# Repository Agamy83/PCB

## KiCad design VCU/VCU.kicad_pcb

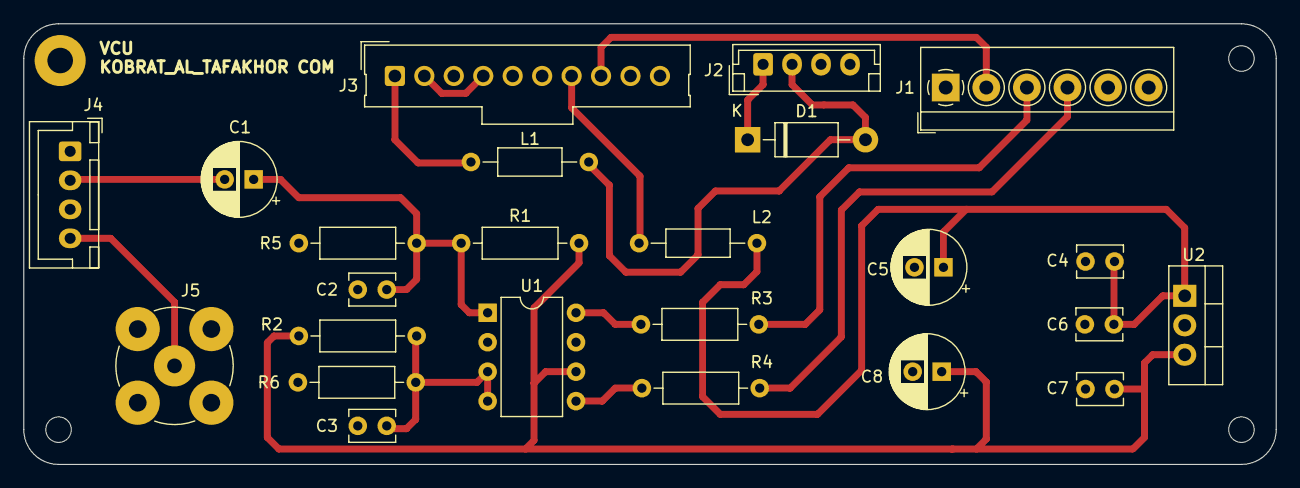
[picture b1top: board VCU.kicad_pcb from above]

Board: 2 copper layers, 108.0 x 38.0 mm, 28 parts (0 on the bottom side), 17 nets.

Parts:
C1: 220u; CP_Radial_D6.3mm_P2.50mm
C2: 680p; C_Disc_D3.8mm_W2.6mm_P2.50mm
C3, C4, C6, C7: 100n; C_Disc_D3.8mm_W2.6mm_P2.50mm
C5: 4u7; CP_Radial_D6.3mm_P2.50mm
C8: 100u; CP_Radial_D6.3mm_P2.50mm
D1: 1N4007; D_DO-41_SOD81_P10.16mm_Horizontal
H1: MountingHole_Pad; MountingHole_2.2mm_M2_Pad
H2, H3, H4: MountingHole; MountingHole_2.2mm_M2
J1: LEMO6; TerminalBlock_4Ucon_1x06_P3.50mm_Horizontal
J2: LEMO4; JST_EH_B4B-EH-A_1x04_P2.50mm_Vertical
J3: Conn_01x10_Male; Molex_SL_171971-0010_1x10_P2.54mm_Vertical
J4: Conn_01x04_Male; JST_XH_B4B-XH-A_1x04_P2.50mm_Vertical
J5: Conn_Coaxial; BNC_TEConnectivity_1478204_Vertical
L1, L2: 1uf; L_Axial_L5.3mm_D2.2mm_P10.16mm_Horizontal_Vishay_IM-1
R1, R2, R6: 10k; R_Axial_DIN0207_L6.3mm_D2.5mm_P10.16mm_Horizontal
R3, R4: 50R; R_Axial_DIN0207_L6.3mm_D2.5mm_P10.16mm_Horizontal
R5: 75R; R_Axial_DIN0207_L6.3mm_D2.5mm_P10.16mm_Horizontal
U1: EL2140; DIP-8_W7.62mm
U2: LM7808_TO220; TO-220-3_Vertical

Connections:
12V: C4.1, C5.1, C6.1, L2.1, U2.1 (VI)
+8V: C7.1, C8.1, R1.2, R2.1, U1.6 (Vcc), U2.3 (VO)
/J1_2_to_J3_8: J1.2, J3.8
/J3_1_to_L2: J3.1, L1.1
/TWISTED_PAIR_out_to_J2: J1.3, R3.2
/TWISTED_PAIR_outb_to_J2: J1.4, R4.2
/Video_1_to_C1: C1.2, J4.2
/Video_2_to_J5: J4.4, J5.1 (In)
GND: C2.2, C3.2, C4.2, C5.2, C6.2, C7.2, C8.2, H1.1, J1.6, J2.4, J3.9, J4.1, J4.3, J5.2 (Ext), R5.2, R6.2, U1.7 (Vee), U2.2 (GND)
unnamed: D1.2 (A), J2.2, L1.2
unnamed: D1.1 (K), J2.1
unnamed: J3.2, J3.4
unnamed: J3.7, L2.2
unnamed: C1.1, C2.1, R1.1, R5.1, U1.1 (Vin)
unnamed: C3.1, R2.2, R6.1, U1.3 (Vinb), U1.4 (Vref)
unnamed: R3.1, U1.8 (Vout)
unnamed: R4.1, U1.5 (Voutb)

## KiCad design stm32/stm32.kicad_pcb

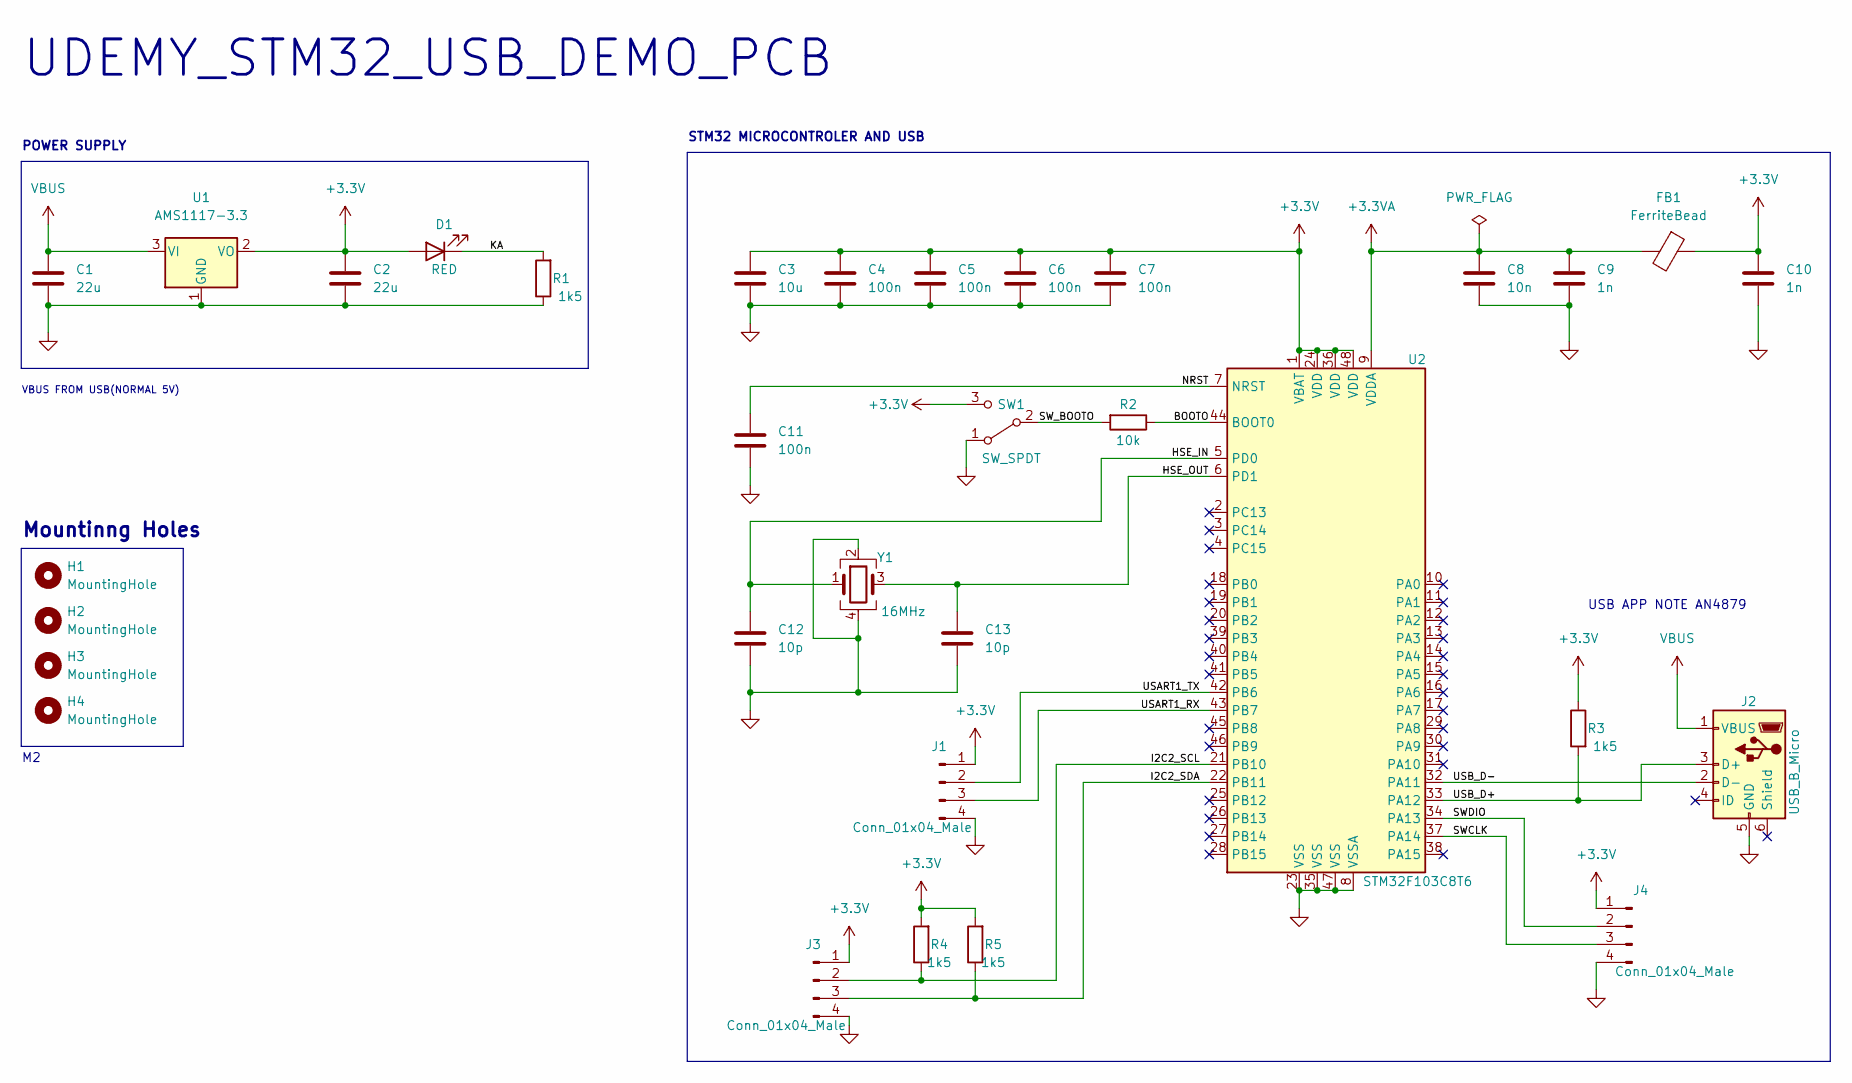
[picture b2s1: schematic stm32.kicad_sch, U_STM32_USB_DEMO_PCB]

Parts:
C1, C2: 22u; C_0805_2012Metric
C3: 10u; C_0603_1608Metric
C4, C5, C6, C7, C11: 100n; C_0402_1005Metric
C8: 10n; C_0402_1005Metric
C9, C10: 1n; C_0402_1005Metric
C12, C13: 10p; C_0402_1005Metric
D1: RED; LED_0603_1608Metric
FB1: FerriteBead; L_0603_1608Metric
H1, H2, H3, H4: MountingHole; MountingHole_2.2mm_M2
J1, J3, J4: Conn_01x04_Male; PinHeader_1x04_P2.54mm_Vertical
J2: USB_B_Micro; USB_Micro-B_Wuerth_629105150521
R1, R3, R4, R5: 1k5; R_0402_1005Metric
R2: 10k; R_0402_1005Metric
SW1: SW_SPDT; SW_SPDT_PCM12
U1: AMS1117-3.3; SOT-223-3_TabPin2
U2: STM32F103C8T6; LQFP-48_7x7mm_P0.5mm
Y1: 16MHz; Crystal_SMD_3225-4Pin_3.2x2.5mm

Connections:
+3.3V: C2.1, C3.1, C4.1, C5.1, C6.1, C7.1, C10.1, D1.2 (A), FB1.1, J1.1, J3.1, J4.1, R3.1, R4.2, R5.2, SW1.3 (C), U1.2 (VO), U2.1 (VBAT), U2.24 (VDD), U2.36 (VDD), U2.48 (VDD)
+3.3VA: C8.1, C9.1, FB1.2, U2.9 (VDDA)
/BOOTO: R2.1, U2.44 (BOOT0)
/HSE_IN: C12.1, U2.5 (PD0), Y1.1
/HSE_OUT: C13.1, U2.6 (PD1), Y1.3
/I2C2_SCL: J3.2, R4.1, U2.21 (PB10)
/I2C2_SDA: J3.3, R5.1, U2.22 (PB11)
/KA: D1.1 (K), R1.2
/NRST: C11.1, U2.7 (NRST)
/SWCLK: J4.3, U2.37 (PA14)
/SWDIO: J4.2, U2.34 (PA13)
/SW_BOOTO: R2.2, SW1.2 (B)
/USART1_RX: J1.3, U2.43 (PB7)
/USART1_TX: J1.2, U2.42 (PB6)
/USB_D+: J2.3 (D+), R3.2, U2.33 (PA12)
/USB_D-: J2.2 (D-), U2.32 (PA11)
GND: C1.2, C2.2, C3.2, C4.2, C5.2, C6.2, C7.2, C8.2, C9.2, C10.2, C11.2, C12.2, C13.2, J1.4, J2.5 (GND), J3.4, J4.4, R1.1, SW1.1 (A), U1.1 (GND), U2.8 (VSSA), U2.23 (VSS), U2.35 (VSS), U2.47 (VSS), Y1.2, Y1.4
VBUS: C1.1, J2.1 (VBUS), U1.3 (VI)

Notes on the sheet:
STM32 MICROCONTROLER AND USB
UDEMY_STM32_USB_DEMO_PCB
Mountinng Holes
USB APP NOTE AN4879
POWER SUPPLY
VBUS FROM USB(NORMAL 5V)

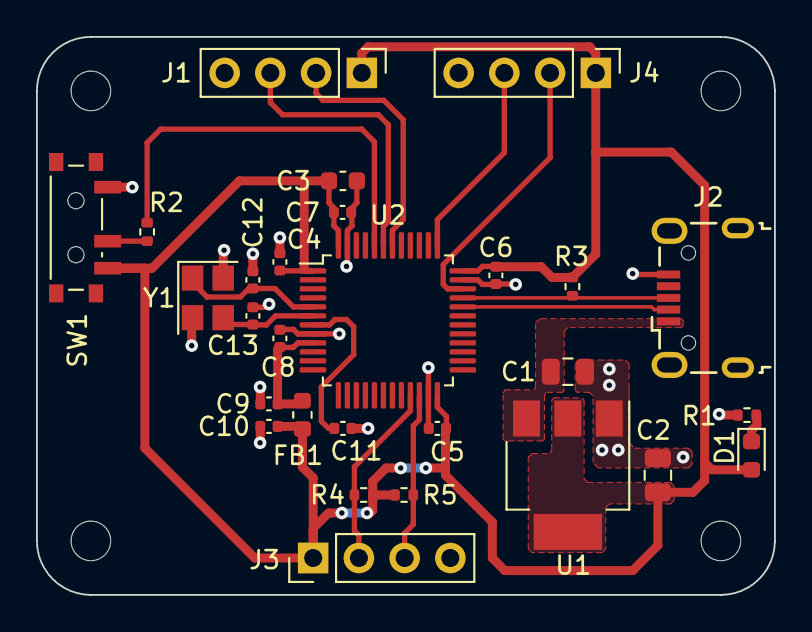
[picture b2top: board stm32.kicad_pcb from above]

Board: 2 copper layers, 41.0 x 31.0 mm, 32 parts (0 on the bottom side), 18 nets.

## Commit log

2022-11-06 moifying power track U2_1 and C7
2022-11-08 gbr modifying
2022-11-08 modifying
2024-03-03 Modifying VCU PCB
2024-03-03 12V Modifying
